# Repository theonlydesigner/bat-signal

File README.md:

# bat-signal badge

## project goals
* **Target Specs:** circular matte black PCB badge with a translucent bat signal window powered by a 3-volt CR2032 coin cell and four yellow DIP LEDs with 100 ohm current limiting resistors.
* **Design Philosophy:** keep the front completely clean by hiding every component on the back and letting light diffuse directly through bare fiberglass where copper and solder mask are stripped away [because hiding your ugly soldering mistakes is peak engineering].
* **Why I'm building this:** hack club holiday hardware swap needed a beginner friendly soldering kit and i wanted to build something that actually looks cool on a backpack instead of another boring blinking square.

## deep brief
this project is a custom through-hole soldering kit designed for the hack club holiday hardware swap. it features a circular matte-black PCB badge with a translucent bat-signal window right in the center. by stripping away copper traces and solder masks on both the top and bottom layers over the bat silhouette and ring, light from the LEDs diffuses cleanly through the bare fiberglass without any distracting shadows or text markings. 

all components mount exclusively on the back side to keep the front face looking pristine. power comes from a 3-volt CR2032 coin cell housed in a socket holder and routed through an SPDT slide switch. the lighting circuit consists of four parallel branches pairing 100-ohm axial resistors with 5-millimeter yellow DIP LEDs. yellow LEDs were chosen specifically for their low two-volt forward voltage which works perfectly with a 3-volt coin cell. the LED legs are bent at 90-degree angles so their domes aim directly inward toward the bat emblem from the left and right wings keeping the entire assembly 100 percent through-hole and well under budget.

## bill of materials (BOM)

| Name | Quantity | Price |
| :--- | :---: | :---: |
| Coin Socket | 5 | 0.63 |
| Lithium Coin Battery | 5 | 1.17 |
| Slide Switch | 5 | 0.15 |
| 100 Ohm Resistor | 26 | 0.15 |
| 5mm LED Yellow | 13 | 0.15 |
| PCB | 5 | 11.30 |
| Big Plastic Ziplock | 5 | 2.70 |
| Small Plastic Zip for small components | 5 | 1.50 |
| Vinyl Sheets for Stickers | 5 | 4.20 |
| **Total** | | **21.95** |

## visual showcase

*(a gorgeous 3d render of the bat signal badge before i burn my fingers with the soldering iron)*

*(the PCB layout showing the stripped fiberglass bat silhouette waiting to glow)*

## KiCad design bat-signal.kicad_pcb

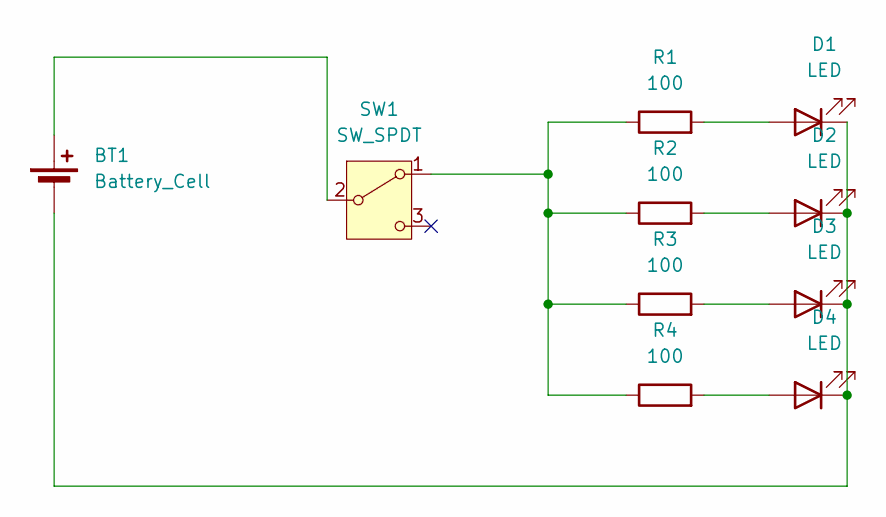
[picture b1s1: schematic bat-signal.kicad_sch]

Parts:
BT1: Battery_Cell; BatteryHolder_Keystone_103_1x20mm
D1, D2, D3, D4: LED; LED_D5.0mm_Horizontal_O1.27mm_Z3.0mm
R1, R2, R3, R4: 100; R_Axial_DIN0207_L6.3mm_D2.5mm_P10.16mm_Horizontal
SW1: SW_SPDT; SW_Slide_SPDT_Straight_CK_OS102011MS2Q

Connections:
unnamed: BT1.1 (+), SW1.2 (B)
unnamed: BT1.2 (-), D1.1 (K), D2.1 (K), D3.1 (K), D4.1 (K)
unnamed: D1.2 (A), R1.2
unnamed: D2.2 (A), R2.2
unnamed: D3.2 (A), R3.2
unnamed: D4.2 (A), R4.2
unnamed: R1.1, R2.1, R3.1, R4.1, SW1.1 (A)

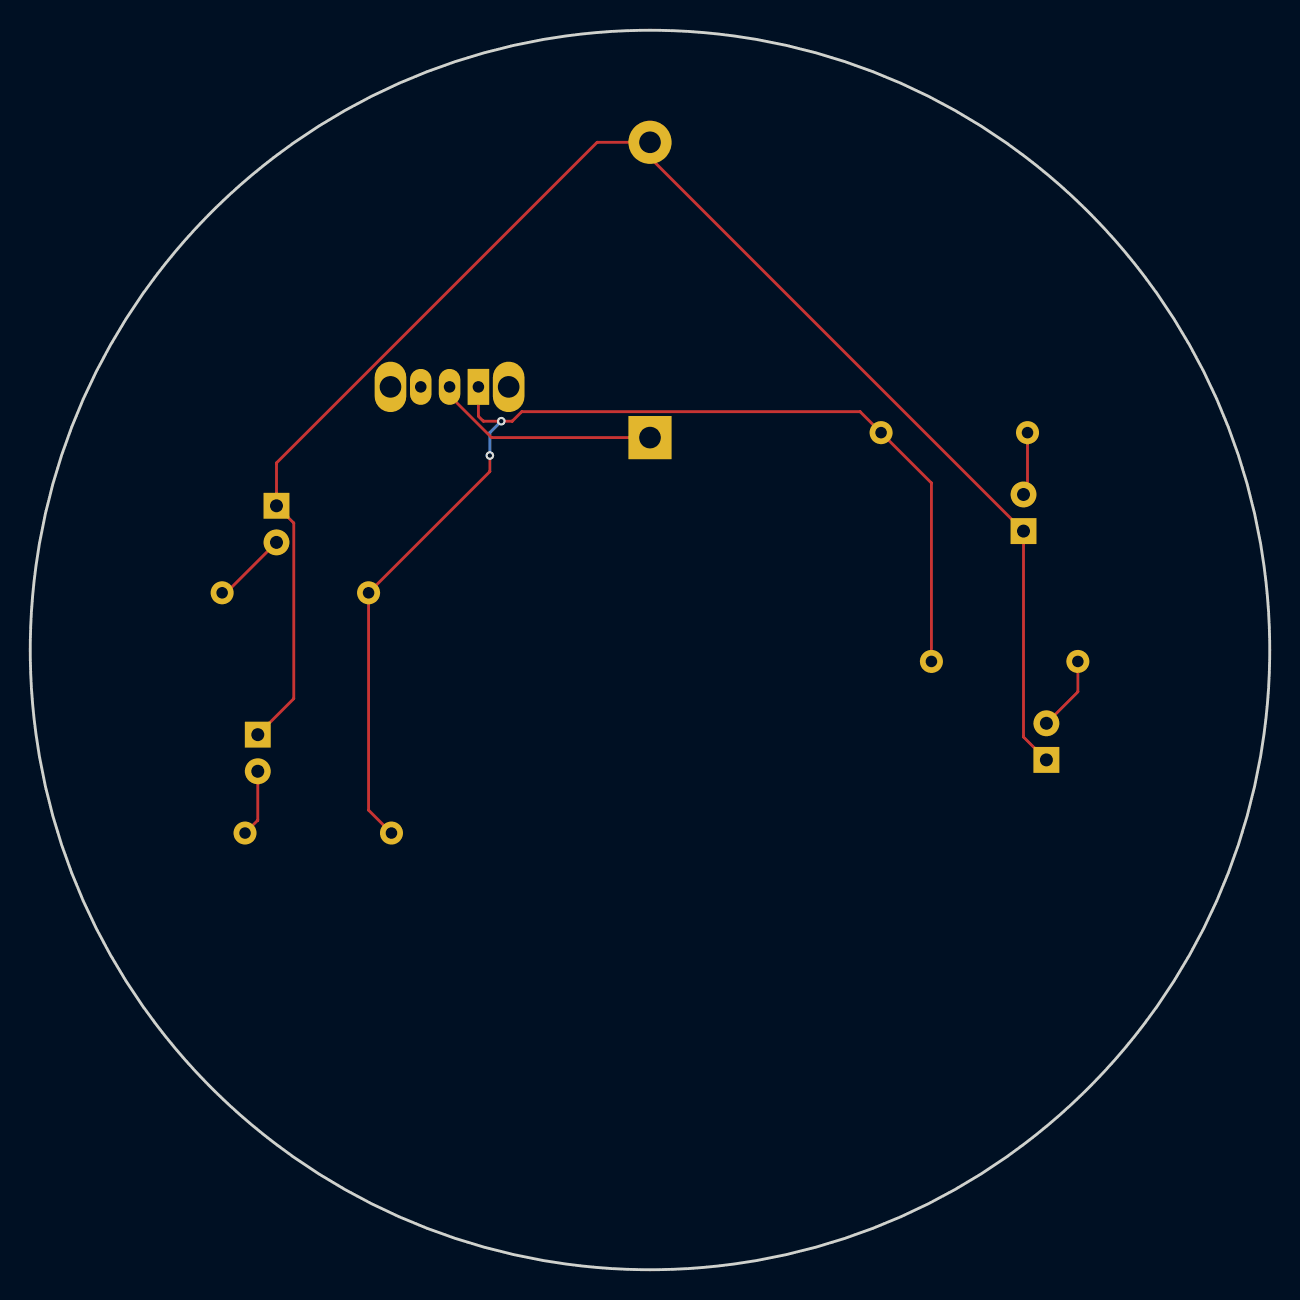
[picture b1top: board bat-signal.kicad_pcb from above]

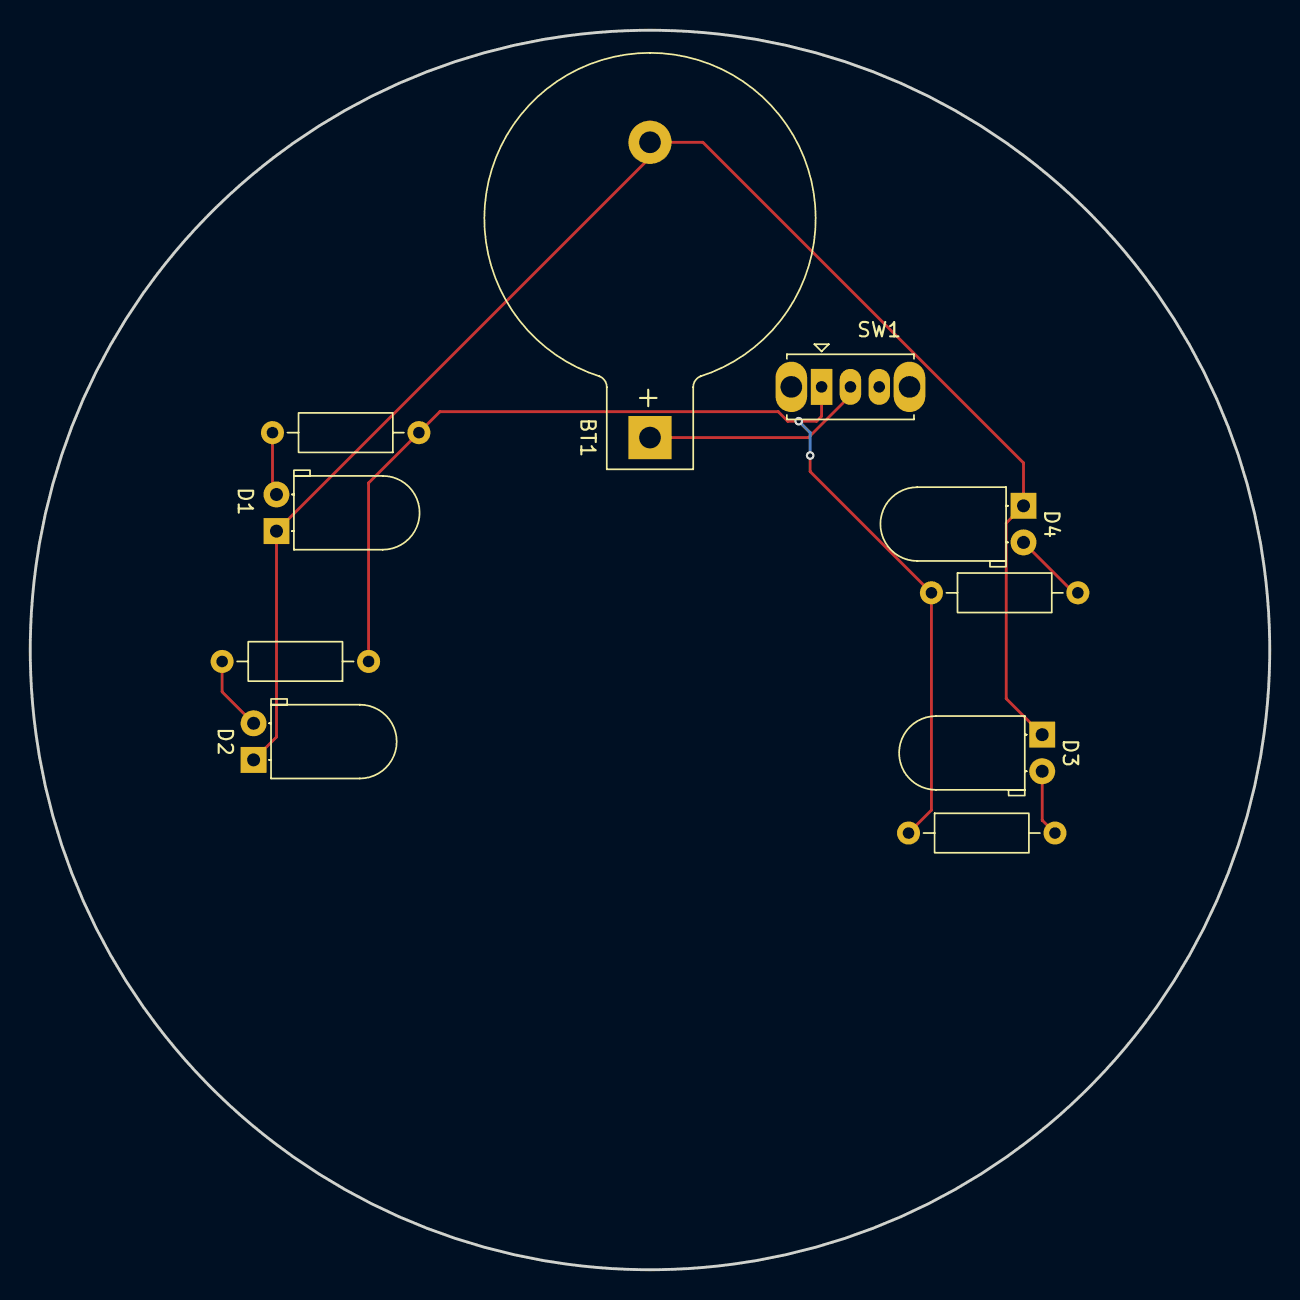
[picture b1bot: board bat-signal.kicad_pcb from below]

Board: 2 copper layers, 86.0 x 86.0 mm, 10 parts (10 on the bottom side), 7 nets.
